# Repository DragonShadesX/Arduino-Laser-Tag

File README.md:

Arduino-Laser-Tag
=================

A repository for my arduino laser tag files

The idea is to create a laser tag system comparable to commercial grade systems found at arenas.

ltag_simple_tagger is a proof of concept build and is for debugging.

ltag_ fire/hit _test are also mainly for debugging.

ltag_custom_your_name_here is the only working full system code.
It is very limited and works, but it doesn't do a whole lot.  Documentation for it is in it's files.

ltag_custom_dragonshadesx is a working build of my tagger.  
So far so good.  There's a lot of comments removed right now because it's still a work in progress and I don't like sorting through it all.
Also because it's 5 in the morning and I want a backup so I can sleep well knowing my code is saved.

libraries is the local libraries you'll need for the files, the only library there right now is from:
http://www.pjrc.com/teensy/td_libs_IRremote.html
This is a modified version of the library originally found at
http://www.righto.com/2009/08/multi-protocol-infrared-remote-library.html
You'll need to replace whatever libraries you have (IRRemoteRobot or whatever) with this if you're using a standard arduino (uno, due, etc).
If you're using a teensy it should come with it's own libraries, just make sure to install them when you run the teensyduino addon.

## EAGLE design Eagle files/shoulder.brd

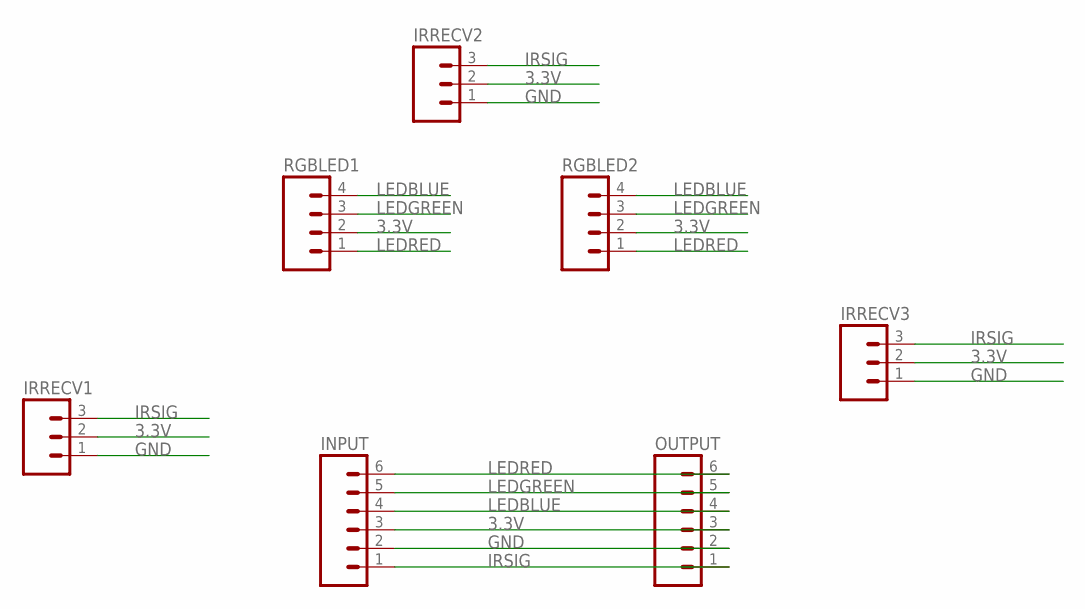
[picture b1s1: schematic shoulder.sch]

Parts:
INPUT: M06SILK_FEMALE_PTH; 1X06
IRRECV1, IRRECV2, IRRECV3: M03PTH; 1X03
OUTPUT: M06SILK_FEMALE_PTH; 1X06
RGBLED1, RGBLED2: M04PTH; 1X04

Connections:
3.3V: INPUT.3, IRRECV1.2, IRRECV2.2, IRRECV3.2, OUTPUT.3, RGBLED1.2, RGBLED2.2
GND: INPUT.2, IRRECV1.1, IRRECV2.1, IRRECV3.1, OUTPUT.2
IRSIG: INPUT.1, IRRECV1.3, IRRECV2.3, IRRECV3.3, OUTPUT.1
LEDBLUE: INPUT.4, OUTPUT.4, RGBLED1.4, RGBLED2.4
LEDGREEN: INPUT.5, OUTPUT.5, RGBLED1.3, RGBLED2.3
LEDRED: INPUT.6, OUTPUT.6, RGBLED1.1, RGBLED2.1

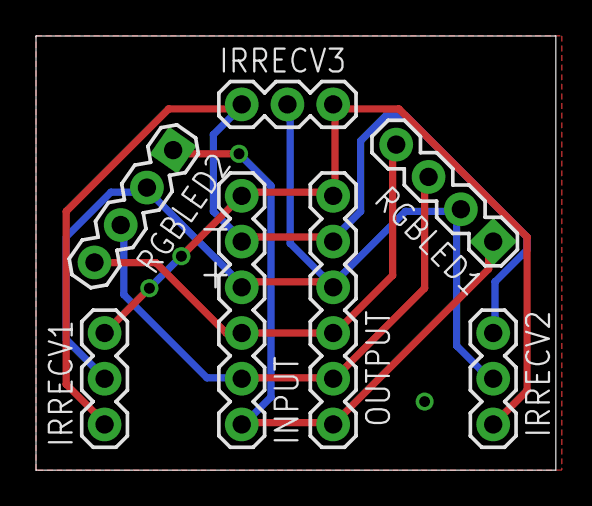
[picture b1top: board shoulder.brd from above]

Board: 2 copper layers, 28.9 x 24.1 mm, 7 parts (0 on the bottom side), 6 nets.

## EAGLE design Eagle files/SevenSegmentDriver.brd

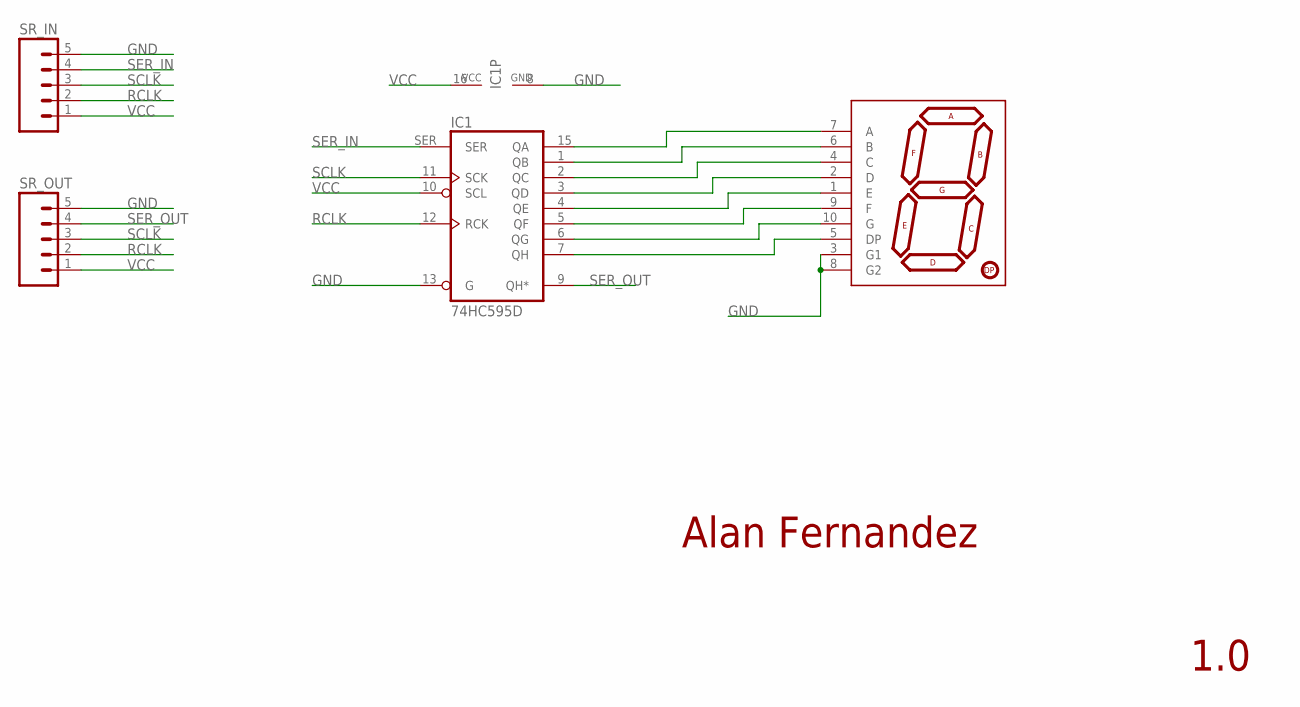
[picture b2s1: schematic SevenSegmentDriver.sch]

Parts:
IC1: 74HC595D; SO16
SR_IN: M05PTH; 1X05
SR_OUT: M05PTH; 1X05
U$1: 7-SEGMENT-DISPLAY-1"-REDEZ; 7-SEGMENT-1"PTH-EZ

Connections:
GND: IC1.8 (GND), IC1.13 (G), SR_IN.5, SR_OUT.5, U$1.3 (G1), U$1.8 (G2)
unnamed: IC1.15 (QA), U$1.7 (A)
unnamed: IC1.1 (QB), U$1.6 (B)
unnamed: IC1.2 (QC), U$1.4 (C)
unnamed: IC1.3 (QD), U$1.2 (D)
unnamed: IC1.4 (QE), U$1.1 (E)
unnamed: IC1.5 (QF), U$1.9 (F)
unnamed: IC1.6 (QG), U$1.10 (G)
unnamed: IC1.7 (QH), U$1.5 (DP)
RCLK: IC1.12 (RCK), SR_IN.2, SR_OUT.2
SCLK: IC1.11 (SCK), SR_IN.3, SR_OUT.3
SER_IN: IC1.SER, SR_IN.4
SER_OUT: IC1.9 (QH*), SR_OUT.4
VCC: IC1.10 (SCL), IC1.16 (VCC), SR_IN.1, SR_OUT.1

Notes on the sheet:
Alan Fernandez
1.0

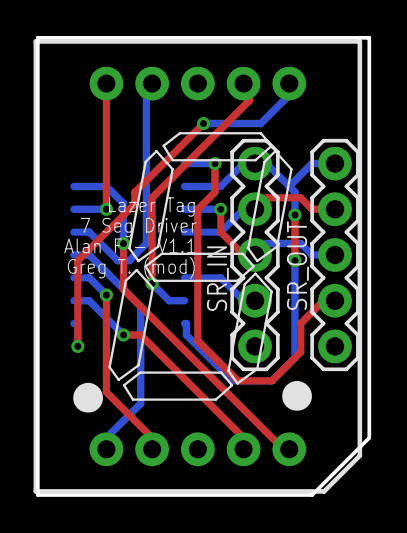
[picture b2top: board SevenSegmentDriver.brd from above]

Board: 2 copper layers, 18.4 x 25.4 mm, 4 parts (1 on the bottom side), 14 nets.

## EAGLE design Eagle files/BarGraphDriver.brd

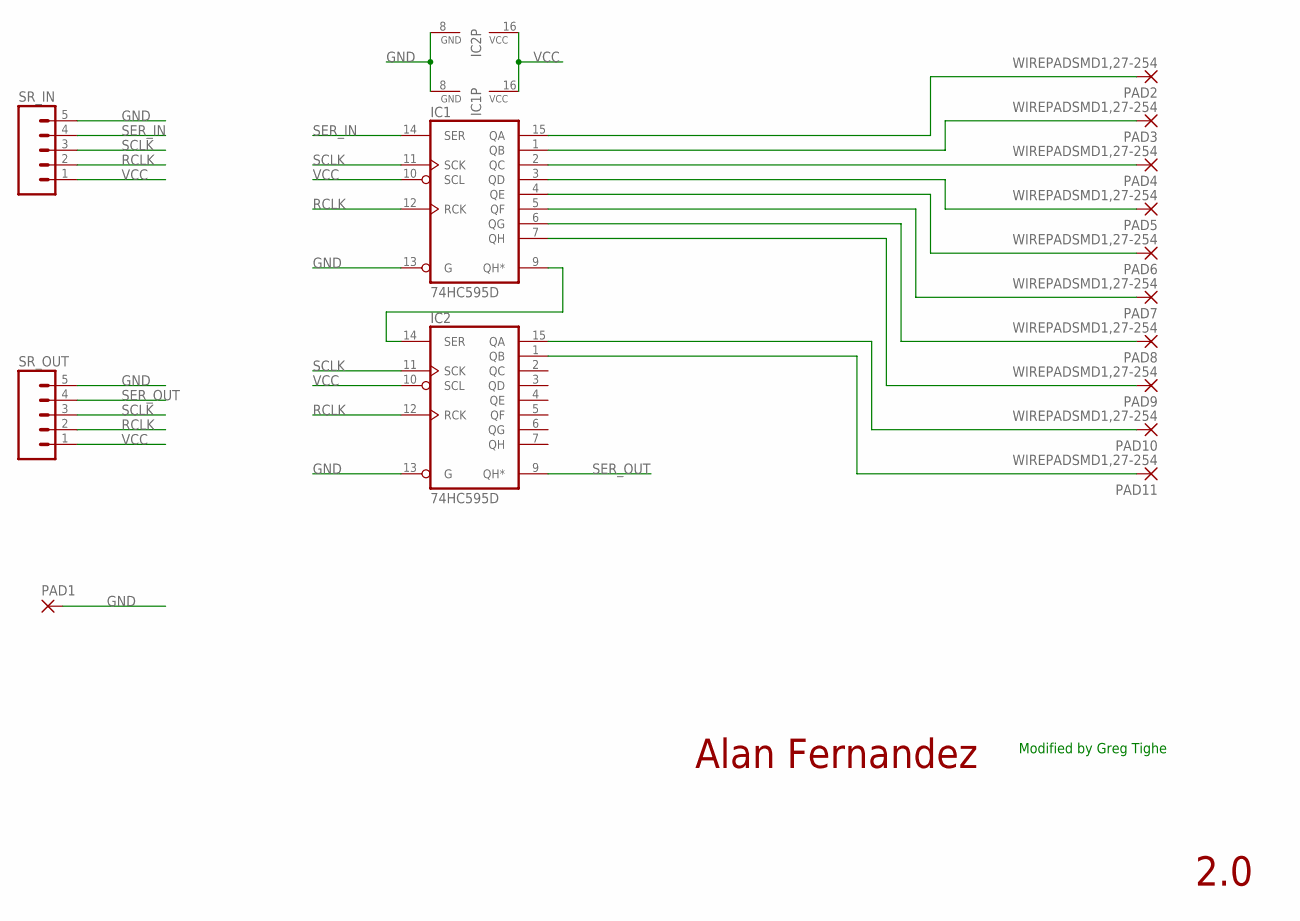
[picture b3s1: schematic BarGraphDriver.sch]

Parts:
IC1, IC2: 74HC595D; SO16
PAD1: SMD2; SMD1,27-2,54
PAD2, PAD3, PAD4, PAD5, PAD6, PAD7, PAD8, PAD9, PAD10, PAD11: WIREPADSMD1,27-254; SMD1,27-2,54
SR_IN: M05PTH; 1X05
SR_OUT: M05PTH; 1X05

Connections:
GND: IC1.8 (GND), IC1.13 (G), IC2.8 (GND), IC2.13 (G), PAD1.1, SR_IN.5, SR_OUT.5
unnamed: IC2.1 (QB), PAD11.1
unnamed: IC1.15 (QA), PAD2.1
unnamed: IC1.1 (QB), PAD3.1
unnamed: IC1.2 (QC), PAD4.1
unnamed: IC1.3 (QD), PAD5.1
unnamed: IC1.4 (QE), PAD6.1
unnamed: IC1.5 (QF), PAD7.1
unnamed: IC1.6 (QG), PAD8.1
unnamed: IC1.7 (QH), PAD9.1
unnamed: IC2.15 (QA), PAD10.1
unnamed: IC1.9 (QH*), IC2.14 (SER)
RCLK: IC1.12 (RCK), IC2.12 (RCK), SR_IN.2, SR_OUT.2
SCLK: IC1.11 (SCK), IC2.11 (SCK), SR_IN.3, SR_OUT.3
SER_IN: IC1.14 (SER), SR_IN.4
SER_OUT: IC2.9 (QH*), SR_OUT.4
VCC: IC1.10 (SCL), IC1.16 (VCC), IC2.10 (SCL), IC2.16 (VCC), SR_IN.1, SR_OUT.1

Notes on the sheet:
Alan Fernandez
2.0
Modified by Greg Tighe

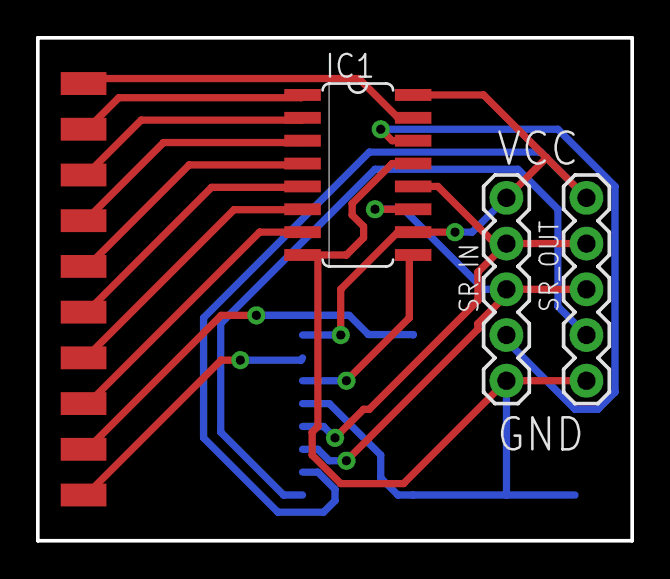
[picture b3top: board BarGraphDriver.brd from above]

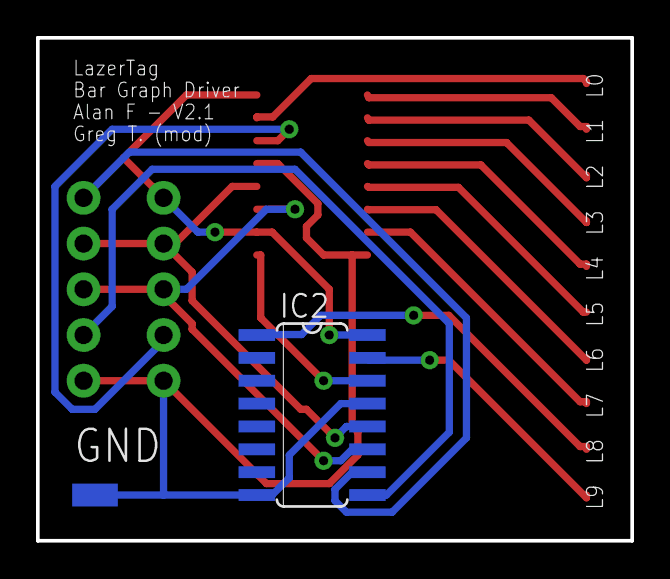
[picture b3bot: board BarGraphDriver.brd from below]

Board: 2 copper layers, 33.0 x 27.9 mm, 15 parts (2 on the bottom side), 17 nets.

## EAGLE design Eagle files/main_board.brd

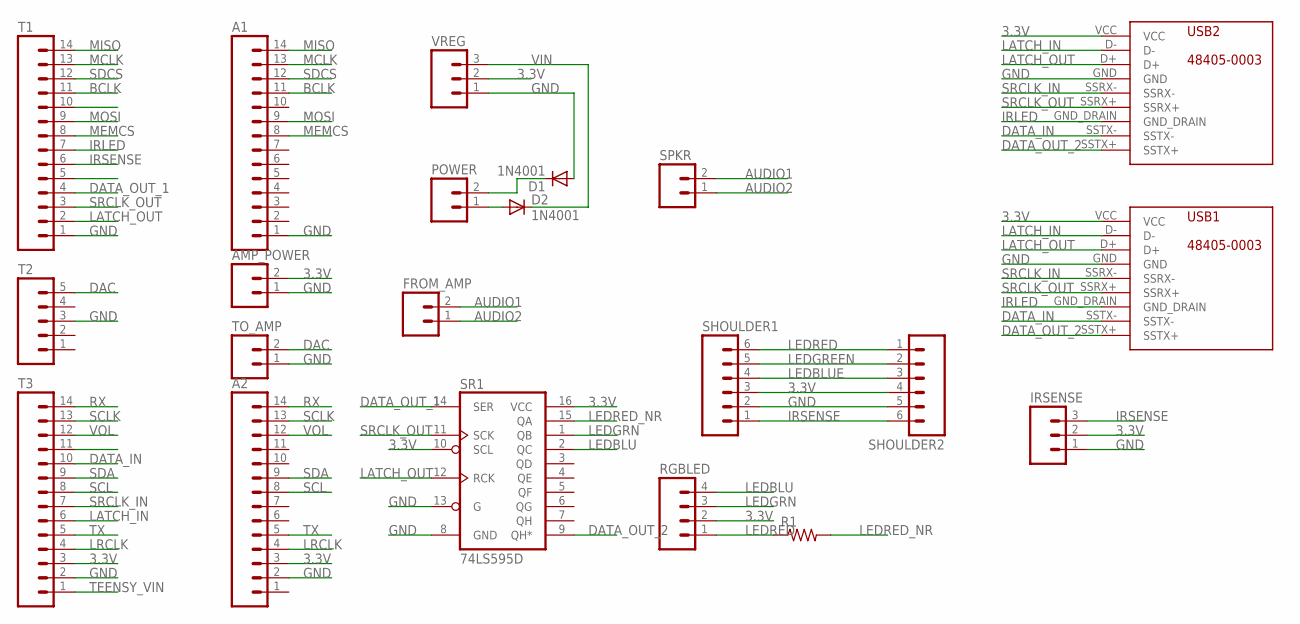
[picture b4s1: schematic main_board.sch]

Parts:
A1, A2: M14; 1X14
AMP_POWER: M02PTH; 1X02
D1, D2: 1N4001; DO41-10
FROM_AMP: M02PTH; 1X02
IRSENSE: M03PTH; 1X03
POWER: M02PTH; 1X02
R1: RESISTOR1206; 1206
RGBLED: M04PTH; 1X04
SHOULDER1, SHOULDER2: M06SILK_FEMALE_PTH; 1X06
SPKR: M02PTH; 1X02
SR1: 74LS595D; SO16
T1, T3: M14; 1X14
T2: M05PTH; 1X05
TO_AMP: M02PTH; 1X02
USB1, USB2: 48405-0003; 48405-0003MYVERSION
VREG: M03PTH; 1X03

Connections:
3.3V: A2.3, AMP_POWER.2, IRSENSE.2, RGBLED.2, SHOULDER1.3, SHOULDER2.4, SR1.10 (SCL), SR1.16 (VCC), T3.3, USB1.VCC, USB2.VCC, VREG.2
AUDIO1: FROM_AMP.2, SPKR.2
AUDIO2: FROM_AMP.1, SPKR.1
BCLK: A1.11, T1.11
DAC: T2.5, TO_AMP.2
DATA_IN: T3.10, USB1.SSTX-, USB2.SSTX-
DATA_OUT_1: SR1.14 (SER), T1.4
DATA_OUT_2: SR1.9 (QH*), USB1.SSTX+, USB2.SSTX+
GND: A1.1, A2.2, AMP_POWER.1, D1.A, IRSENSE.1, SHOULDER1.2, SHOULDER2.5, SR1.8 (GND), SR1.13 (G), T1.1, T2.3, T3.2, TO_AMP.1, USB1.GND, USB2.GND, VREG.1
IRLED: T1.7, USB1.GND_DRAIN, USB2.GND_DRAIN
IRSENSE: IRSENSE.3, SHOULDER1.1, SHOULDER2.6, T1.6
LATCH_IN: T3.6, USB1.D-, USB2.D-
LATCH_OUT: SR1.12 (RCK), T1.2, USB1.D+, USB2.D+
LEDBLU: RGBLED.4, SR1.2 (QC)
LEDBLUE: SHOULDER1.4, SHOULDER2.3
LEDGREEN: SHOULDER1.5, SHOULDER2.2
LEDGRN: RGBLED.3, SR1.1 (QB)
LEDRED: R1.1, RGBLED.1, SHOULDER1.6, SHOULDER2.1
LEDRED_NR: R1.2, SR1.15 (QA)
LRCLK: A2.4, T3.4
MCLK: A1.13, T1.13
MEMCS: A1.8, T1.8
MISO: A1.14, T1.14
MOSI: A1.9, T1.9
unnamed: D2.A, POWER.1
unnamed: D1.C, POWER.2
RX: A2.14, T3.14
SCL: A2.8, T3.8
SCLK: A2.13, T3.13
SDA: A2.9, T3.9
SDCS: A1.12, T1.12
SRCLK_IN: T3.7, USB1.SSRX-, USB2.SSRX-
SRCLK_OUT: SR1.11 (SCK), T1.3, USB1.SSRX+, USB2.SSRX+
TEENSY_VIN: T3.1
TX: A2.5, T3.5
VIN: D2.C, VREG.3
VOL: A2.12, T3.12

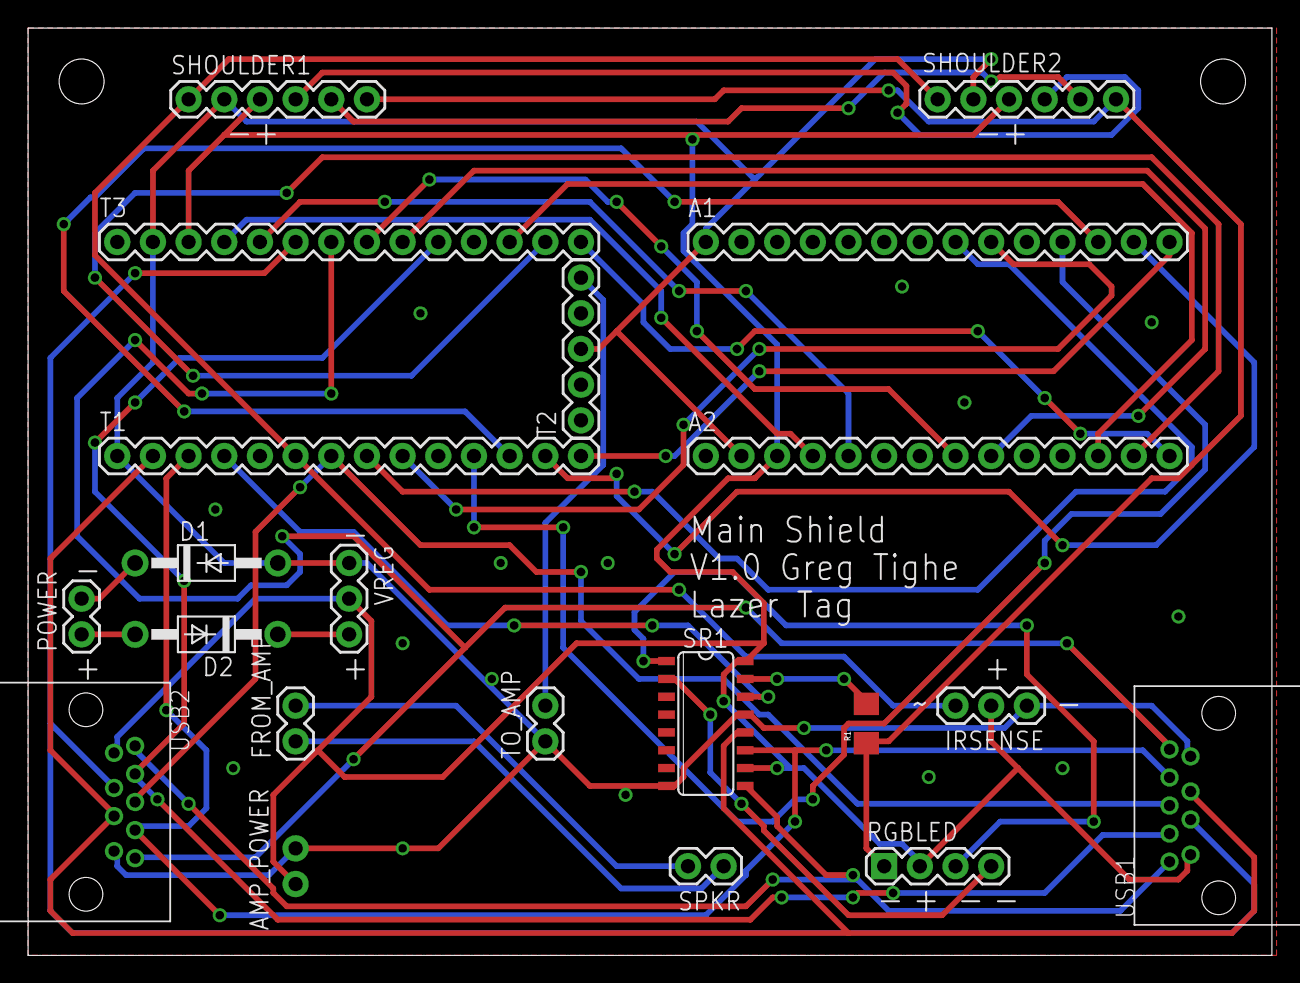
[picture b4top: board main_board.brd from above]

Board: 2 copper layers, 88.6 x 66.0 mm, 21 parts (1 on the bottom side), 36 nets.

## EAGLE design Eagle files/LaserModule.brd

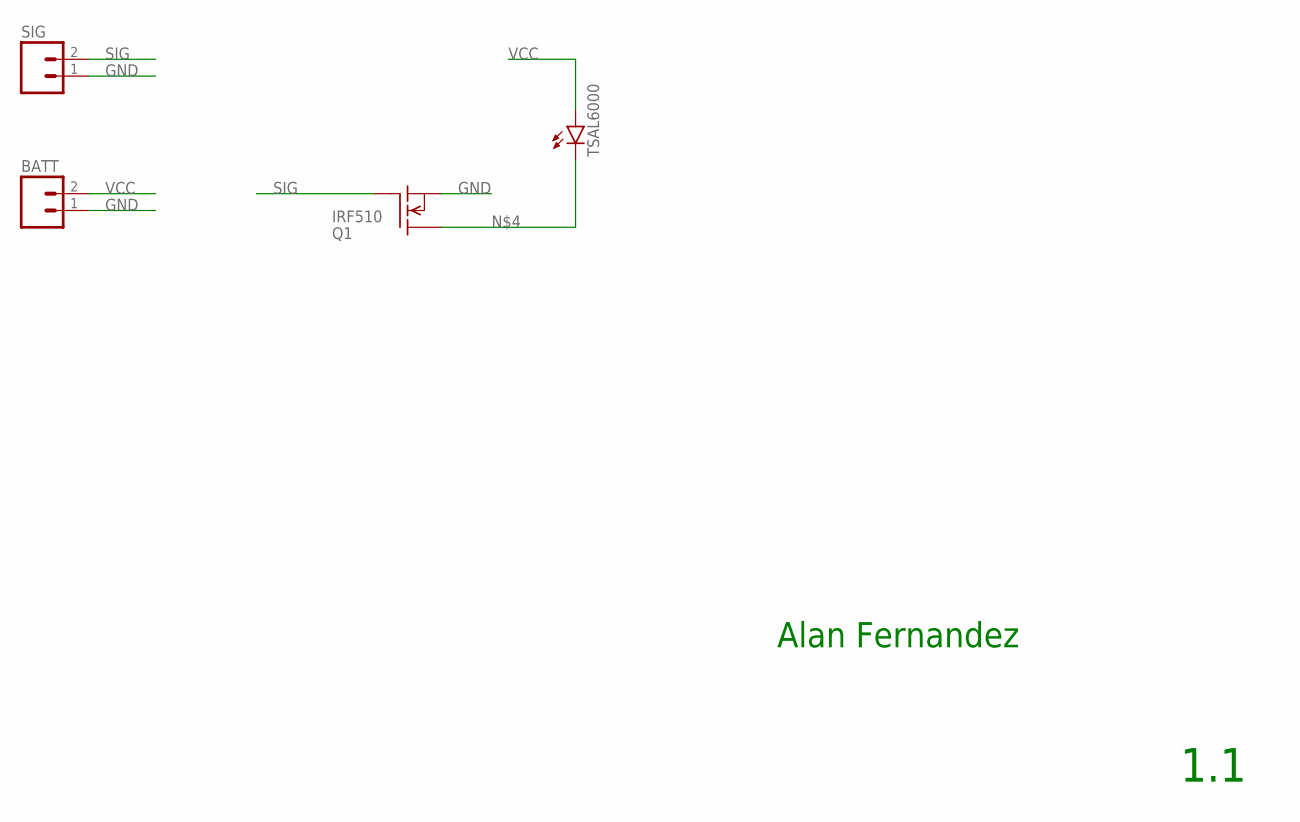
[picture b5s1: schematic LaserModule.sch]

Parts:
BATT: M02PTH; 1X02
Q1: IRF510; TO220
SIG: M02PTH; 1X02
TSAL6000: LED5MM

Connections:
GND: BATT.1, Q1.3 (S), SIG.1
unnamed: Q1.2 (D), TSAL6000.K (C)
SIG: Q1.1 (G), SIG.2
VCC: BATT.2, TSAL6000.A

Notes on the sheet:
Alan Fernandez
1.1

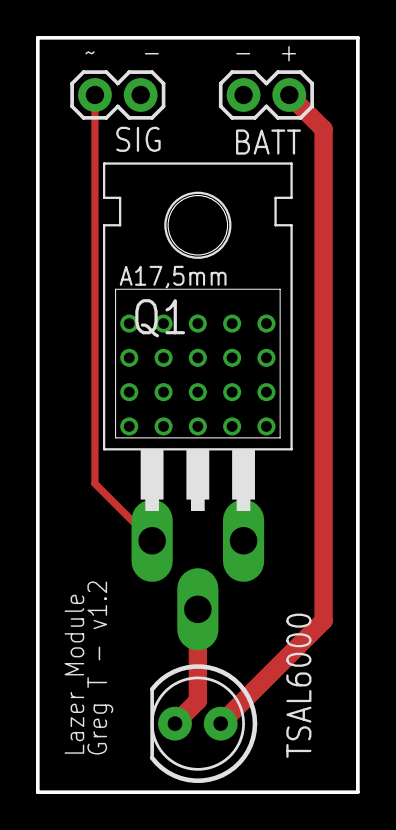
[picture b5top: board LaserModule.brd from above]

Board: 2 copper layers, 17.8 x 41.9 mm, 4 parts (0 on the bottom side), 4 nets.

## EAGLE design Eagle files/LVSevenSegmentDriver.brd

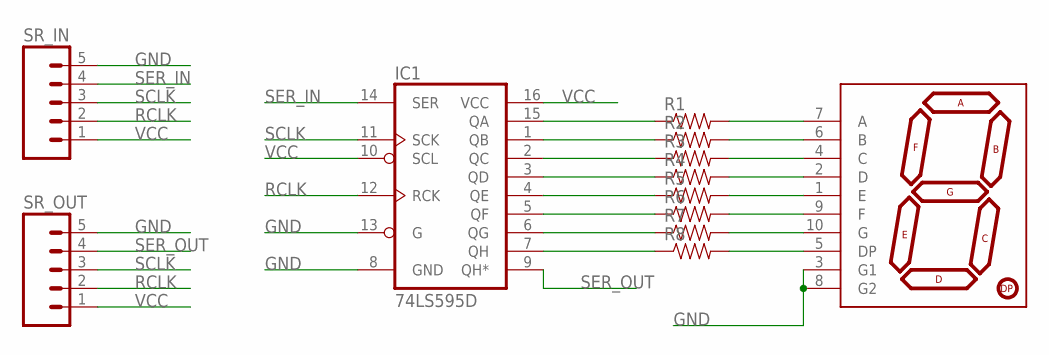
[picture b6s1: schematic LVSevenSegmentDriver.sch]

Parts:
IC1: 74LS595D; SO16
R1, R2, R3, R4, R5, R6, R7, R8: RESISTOR1206; 1206
SR_IN: M05PTH; 1X05
SR_OUT: M05PTH; 1X05
U$1: 7-SEGMENT-DISPLAY-1"-REDEZ; 7-SEGMENT-1"PTH-EZ

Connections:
GND: IC1.8 (GND), IC1.13 (G), SR_IN.5, SR_OUT.5, U$1.3 (G1), U$1.8 (G2)
unnamed: IC1.15 (QA), R1.1
unnamed: R1.2, U$1.7 (A)
unnamed: IC1.1 (QB), R2.1
unnamed: R2.2, U$1.6 (B)
unnamed: IC1.2 (QC), R3.1
unnamed: R3.2, U$1.4 (C)
unnamed: IC1.3 (QD), R4.1
unnamed: R4.2, U$1.2 (D)
unnamed: IC1.4 (QE), R5.1
unnamed: R5.2, U$1.1 (E)
unnamed: IC1.5 (QF), R6.1
unnamed: R6.2, U$1.9 (F)
unnamed: IC1.6 (QG), R7.1
unnamed: R7.2, U$1.10 (G)
unnamed: IC1.7 (QH), R8.1
unnamed: R8.2, U$1.5 (DP)
RCLK: IC1.12 (RCK), SR_IN.2, SR_OUT.2
SCLK: IC1.11 (SCK), SR_IN.3, SR_OUT.3
SER_IN: IC1.14 (SER), SR_IN.4
SER_OUT: IC1.9 (QH*), SR_OUT.4
VCC: IC1.10 (SCL), IC1.16 (VCC), SR_IN.1, SR_OUT.1

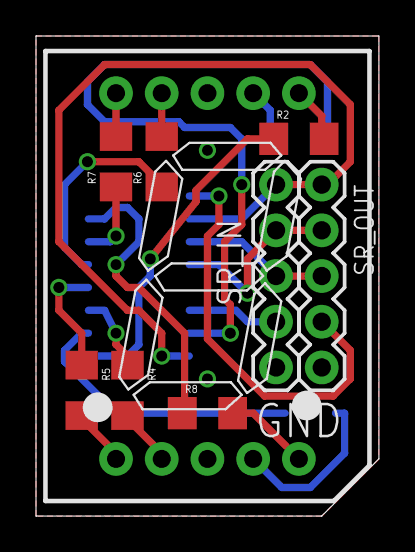
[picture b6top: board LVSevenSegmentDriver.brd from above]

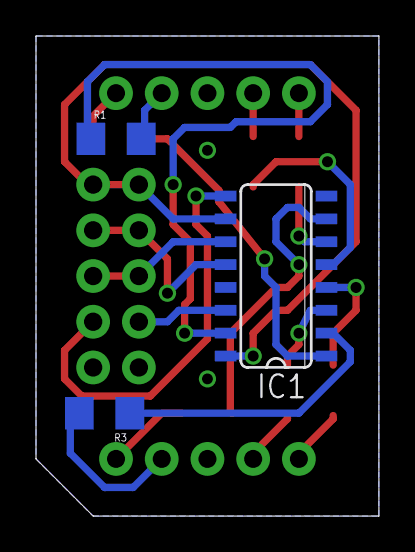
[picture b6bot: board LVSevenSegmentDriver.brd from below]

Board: 2 copper layers, 19.1 x 26.7 mm, 12 parts (3 on the bottom side), 22 nets.

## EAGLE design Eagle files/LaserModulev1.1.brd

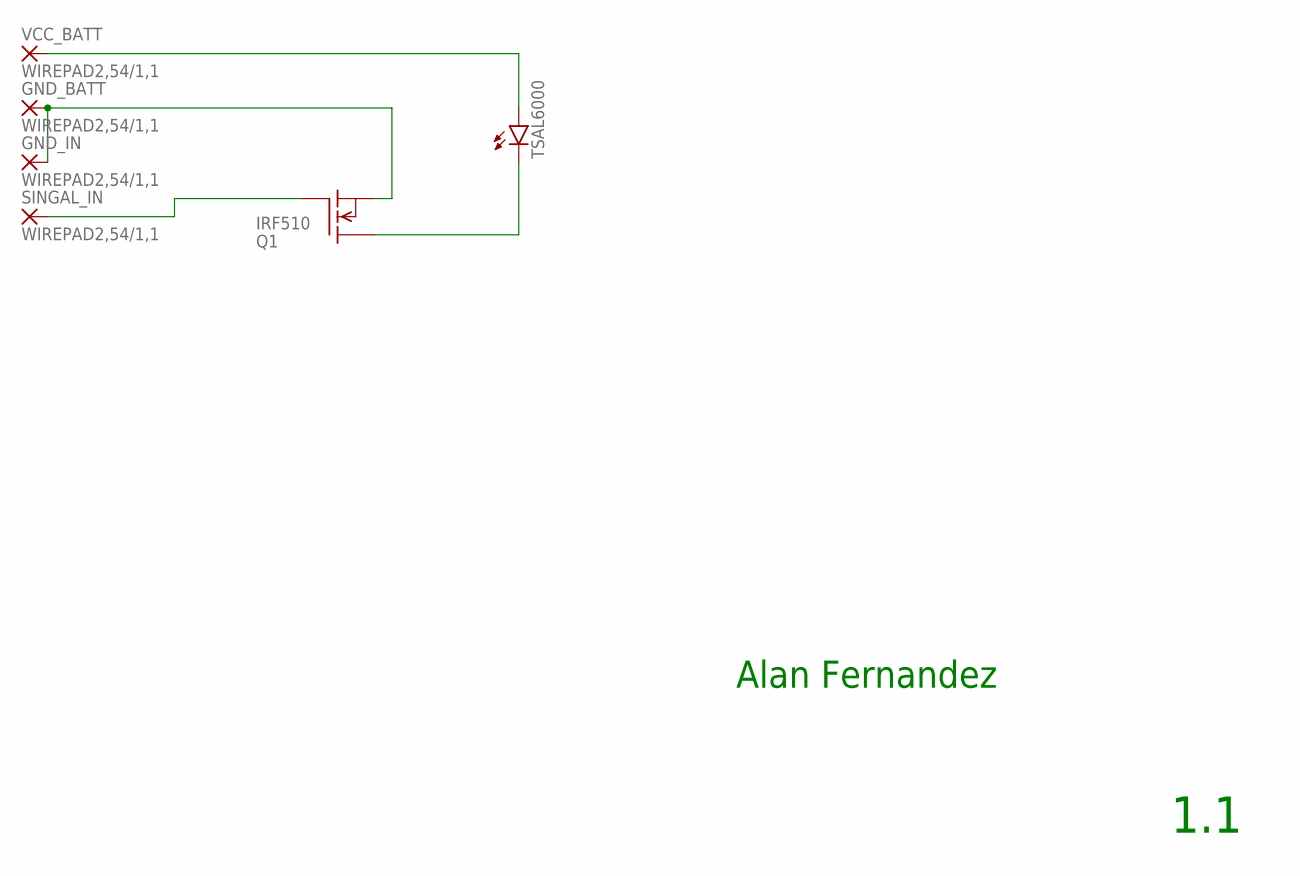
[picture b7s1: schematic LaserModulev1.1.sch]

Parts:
GND_BATT: WIREPAD2,54/1,1; 2,54/1,1
GND_IN: WIREPAD2,54/1,1; 2,54/1,1
Q1: IRF510; TO220
SINGAL_IN: WIREPAD2,54/1,1; 2,54/1,1
TSAL6000: LED5MM
VCC_BATT: WIREPAD2,54/1,1; 2,54/1,1

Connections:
GND: GND_BATT.1, GND_IN.1, Q1.3 (S)
unnamed: Q1.1 (G), SINGAL_IN.1
unnamed: TSAL6000.A, VCC_BATT.1
unnamed: Q1.2 (D), TSAL6000.K (C)

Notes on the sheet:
Alan Fernandez
1.1

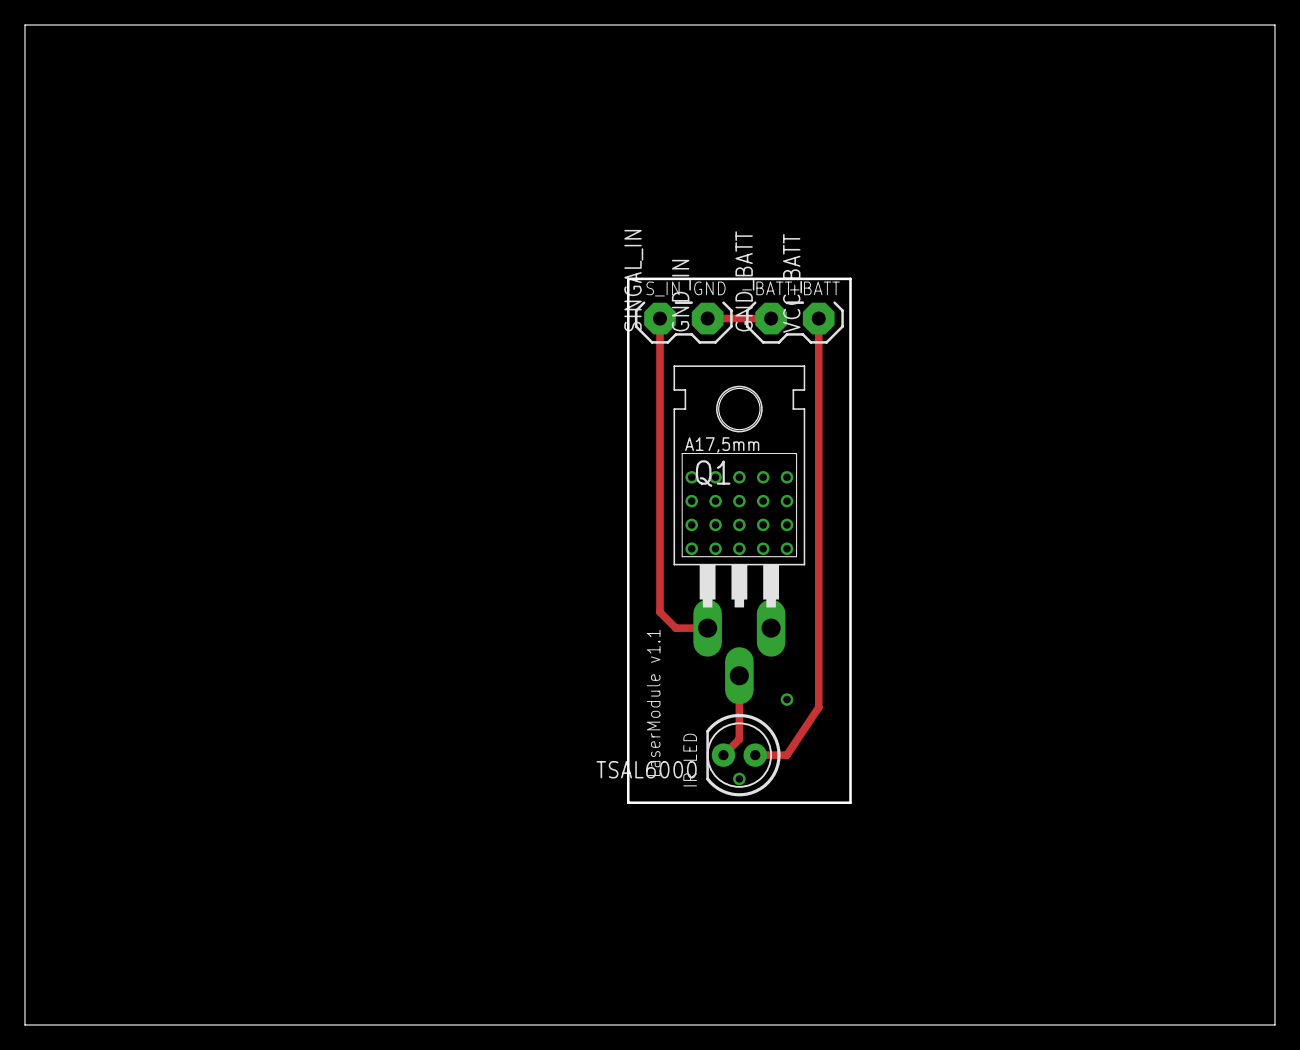
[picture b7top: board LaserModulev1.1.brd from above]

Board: 2 copper layers, 99.8 x 79.8 mm, 6 parts (0 on the bottom side), 4 nets.

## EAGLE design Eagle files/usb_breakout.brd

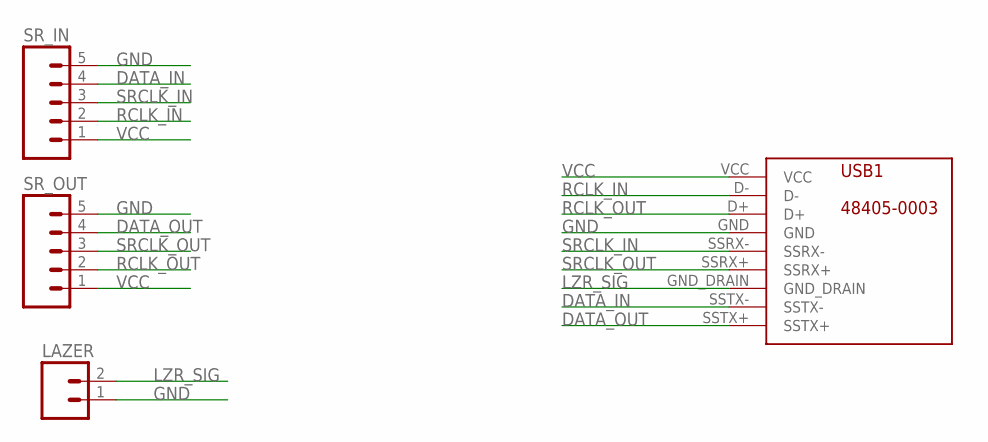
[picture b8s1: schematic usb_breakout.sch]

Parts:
LAZER: M02PTH; 1X02
SR_IN: M05PTH; 1X05
SR_OUT: M05PTH; 1X05
USB1: 48405-0003; 48405-0003MYVERSION

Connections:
DATA_IN: SR_IN.4, USB1.SSTX-
DATA_OUT: SR_OUT.4, USB1.SSTX+
GND: LAZER.1, SR_IN.5, SR_OUT.5, USB1.GND
LZR_SIG: LAZER.2, USB1.GND_DRAIN
RCLK_IN: SR_IN.2, USB1.D-
RCLK_OUT: SR_OUT.2, USB1.D+
SRCLK_IN: SR_IN.3, USB1.SSRX-
SRCLK_OUT: SR_OUT.3, USB1.SSRX+
VCC: SR_IN.1, SR_OUT.1, USB1.VCC

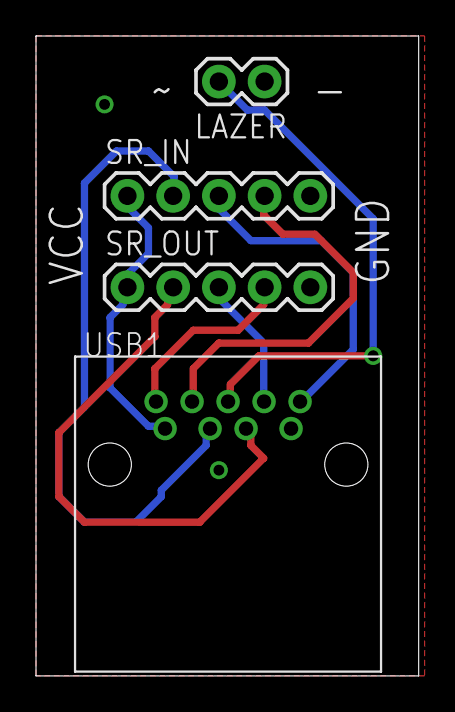
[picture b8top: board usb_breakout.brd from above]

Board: 2 copper layers, 21.3 x 35.5 mm, 4 parts (0 on the bottom side), 9 nets.

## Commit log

2014-08-11 V1.0 and V1.1
    New files for the default taggers
2014-08-11 Rules/BOM
    Added the rules for designing a tagger and the current BOM for said
    tagger
2014-08-13 Fixes to 1.1
    Added burst count option, strengthened health check for "dying" and
    added a check so that the update displays function would be called only
    when health or ammo changed instead of every time the loop ran to save
    processor power.
2014-08-18 New version of tagger
    The 1.2 code removes the need for hardware control of the IR LED
    frequency and the BOM has been changed to match. (Confused? Sorry,
    I'll put up circuit diagrams soon that will make this much more clear)
2014-11-27 Minor changes and a new tagger
    Minor bug fixes to V1.2, such as the fact that passing a duration to
    tone() does not also count as a delay (whoops).
    The new file is a set of basic firmware for the prototype soon to be
    built inside a cheap plastic "gun" housing for a play station move
    controller. (Yeah "gun" shapes are against the rules but this allows me
    to test accuracy in a frame type I know and can aim very easily/well, as
2015-08-31 New test files
    Just for dev purposes. These two files are a good way to test hardware
    setups and whether you have the right libraries.
2015-09-04 Demo File
    Just a demo, to prove that everything works. Repo cleanup coming soon.
2015-09-05 Cleaned up the repo
    Removed old and broken files, from here on out I am trying to actually
    use source control correctly.
2015-09-07 Custom DIY Tagger Template
    These are the files for a custom DIY tagger. Currently they compile but
    have not been tested yet. Hardware prototypes need some modifications
    before that happens, and I wanted to get these files up as soon as they
    were done. Inevitable bugfixes soon.
2015-09-08 Bugfixes
    The inevitable bugfixes. Everything is tested and works now.
2015-09-08 Added Library
    Added the correct library and updated the README. These changes
    *should* allow anyone to clone this to their computer and use it as an
    Arduino Workspace.
2015-09-26 Remove admin
    Did not know if Nick was still up for being an Admin so I removed him
    from the admin list.
2015-10-17 Something broke
    I have no idea what happened but all of a sudden nothing works so I'm
    nuke-ing everything but the actual code and we're going from there.
2015-10-17 New tagger, library fixes (I hope)
    I finally got my tagger hardware up and running, although the haptic
    feedback is giving me loads of trouble, but this code works for now.
    Solenoid "click" feedback is disabled, everything else works. Still no
    team support yet though.
2015-11-20 Shift Registers!
    Added shift register support for the trigger and reload pins, giving
    ability for a d-pad interface if needed later.
2016-01-12 Library and Readme changes
    Added new libraries and updated the readme with links for future
    updating
2016-03-18 Prep for ISP
    Moved a bunch of old and broken stuff out of the main folder so clean up
    the repo in preparation for the ISP
2016-03-23 New Stuff
    Shopping list and Message Format docs completed.
2016-03-25 New parts
    Added a few things to the shopping list I forgot in my tiredness last
    night
2016-03-31 PCBs
    Changes to shopping list, new folder added for PCBs
2016-03-31 >:|
    New blank file to get the Eagle file to show up on github.com
2016-03-31 Adds new firmware
2016-04-01 Bar Graph Driver V 2.0
    Bar Graph Driver board and schematic.
2016-04-01 Bar Graph Driver V 2.0
    Bar Graph Driver board and schematic. Ready for prototyping.
2016-04-03 Cleaning
    Deleted duplicate files that weren't uploaded into the right folder.
2016-04-03 New Boards
    Finished the first version of some new boards. They will need to be
    re-looked at when I'm less tired.
2016-04-03 Library
    Added my custom library for the USB3.0 connector breakout.
2016-04-03 Seven Segment Driver Boards
    LVSevenSegment is for low voltage displays like the Red display. It contains resistors to limit the current. The other design has no resistors. The design with resistors is surprisingly smaller than 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
2016-04-04 Ready for Fabbing
    Silk Screens added and last minute DRC checks done.
2016-04-04 Prep for oshpark
    Changed naming of BarGraphDriver to be more accurate, added a new bar
    graph driver for non-lv boards, fixed the usb breakout to match our
    standards and removed the text doc.
2016-04-04 Fixes
    Removed outer footprint of board so that each board is now the correct
    size instead of that of the default footprint.
2016-04-04 Minor fixes
    Added + and - on a few things to help differentiate what is what and
    when we need to flip the ribbon cable.
2016-04-05 aaaaaaaaaaaaaaaaaaaaaaaaaaaaaaaaaaaa
    Cleaned up schematics, replaced wire solder points with header pin
    mounts for standardization, recreated a broken file and dealt with the
    confusion and insanity that followed.
2016-04-05 FIRE TEH LAZOR!
    Modules for all your laser firing needs.
2016-04-05 Super Fresh
    These boards are damn sexy.
2016-04-05 New Lazer
    Changed some stuff in the laser module, nbd.
2016-04-05 Fresher
    Last "super fresh" board wasn't fresh enough. Only real fix was
    assigning a via to a net and expanding the groundplane boundaries.
2016-04-06 Fixes
    more fixes >:|
    should e ready for fabbing
2016-04-06 moar fixes >:|
    I would say it's now ready to fab but who knows.
2016-04-10 New Message Format
    Updated and changed to reflect all the new capabilities.
2016-04-11 Admin Tool
    First version of the admin tool firmware. No "lazer" functionality or
    comments yet.
2016-04-12 Admin Tool
    Completed the Admin Tool firmware and updated the standards doc with new
    info.
2016-04-15 Updates
    Disabled LED blink in the admin tool firmware, not sure about the other
    updates.
2016-04-26 Much Functionality Added
    New file containing lots of new functionality added. Kept the old for
    reference purposes.
    To be implemented:
    -Fire Modes
    -Display Update
    Other Functions should be tested for correct behavior
2016-04-28 Moar Functionality!
    This code should be working. It needs the display functions added so
    that it can display stuff.... Need to test with actual hardware to debug
    although software tests suggest that it can receive hits, kill player,
    track respawns, set new configurations.
    Supposedly, it can shoot and reload. Have not tested.
2016-04-29 Fixes and Functionality
    Fixed the shift by 8 instead of 4 for the admin tool (Greg was sleepy).
    Added functionality for shooting. The configure tagger function now
    creates a custom packet to send when the trigger is pressed ie. It can
    now shoot.
    (Fingers crossed)
2016-04-29 EPIC Bit Shifting Magic
    Shifted all the bits and the tagger can now create its own packet to
    shoot enemies PEW PEW PEW!
2016-04-29 Formatting and Comments
    Added a couple of comments
2016-05-01 Merges Jake's and Alan's code; Adds Support for Updating Displays
    Also gets rid of camel case. Sorry Alan. I miss it too. :/
2016-05-01 Compatibility and More
    Added compatibility with LTX taggers. Made changes to function that
    generates the send packet.
    Need testing ASAP.
2016-05-01 Adds Support for Team Colors. And it's Broken. -_-
    stupid obscure compiler errors
2016-05-01 Fixed Lots of BS
    Fixed GitHub going nuts and duplicating stuff. Fixed team_color issues
    by adding new function color_assigner. (This is a lazy hack fix)
2016-05-02 Adds Audio Functionality
    Not all sfx are done yet, but here's a few.
2016-05-02 Erased duplicates
    Founds some duplicates and erased
2016-05-02 Changes for debugging
2016-05-02 Chnages for debugging
2016-05-03 Commented out audio
2016-05-03 New Code
    It has come to this point. Again.
2016-05-03 Cram time
    Updates to admin tool to help debug
    Small changes to the message format file to help figure out what's going
    on
    New firmware that removes most of the functionality of the main code,
    should only work with ltx taggers in ffa mode but for some reason the
    pulse data is not being sent correctly.
2016-05-03 still dead
    Doesn't work for some reason. The data that is being given to the send
    function is not what is being received.

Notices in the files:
parts and their libraries:
SparkFun-Resistors: Licensing: Creative Commons ShareAlike 4.0 International - https://creativecommons.org/licenses/by-sa/4.0
